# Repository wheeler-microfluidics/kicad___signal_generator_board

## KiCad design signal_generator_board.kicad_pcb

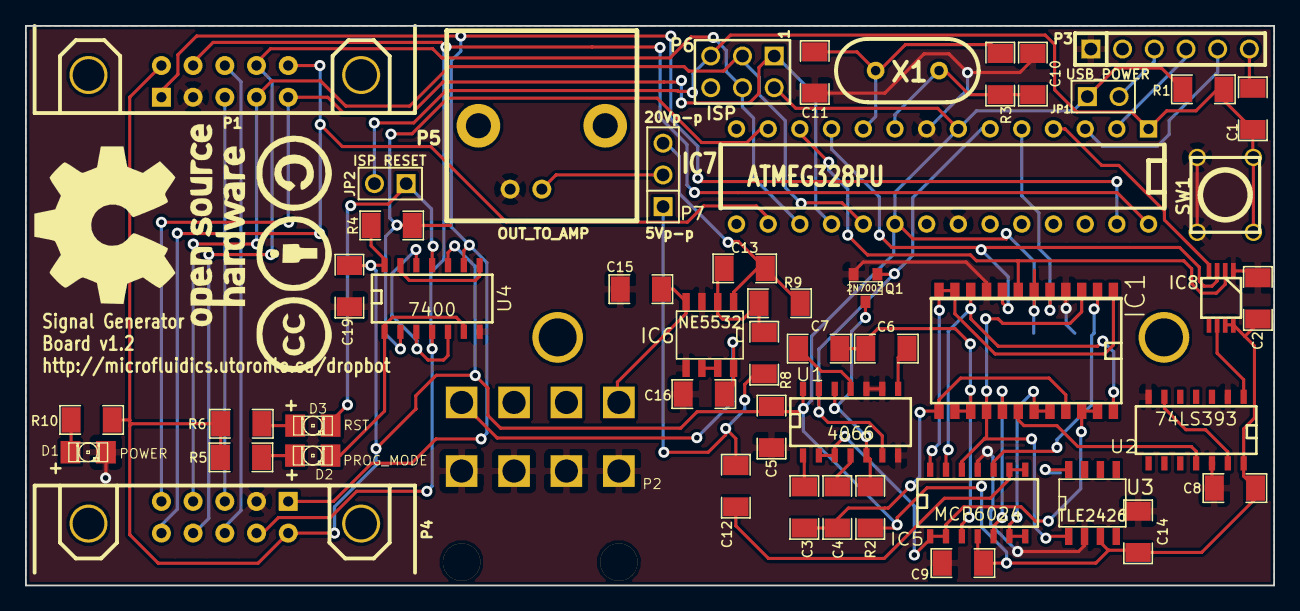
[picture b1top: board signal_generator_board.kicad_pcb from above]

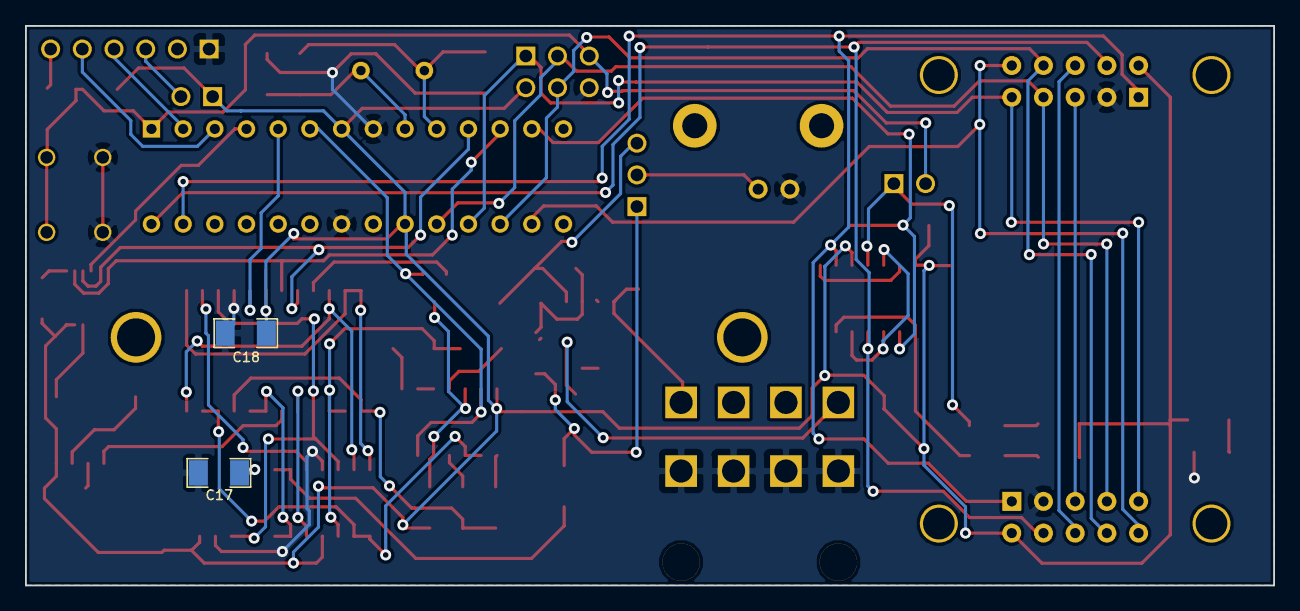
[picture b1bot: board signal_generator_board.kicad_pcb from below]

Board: 2 copper layers, 100.0 x 44.8 mm, 54 parts (2 on the bottom side), 56 nets.

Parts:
1PIN, 1PIN#2: P***; 1pin
C1, C2, C5, C8, C9, C14, C15, C16, C17, C18, C19: 0.1uF; SM1206
C3: 47nF; SM1206
C4: 4.7nF; SM1206
C6: 6.8nF; SM1206
C7: 680pF; SM1206
C10, C11: 22pF; SM1206
C12: 1uF; SM1206
C13: 5pF; SM1206
D1: POWER; LED-1206
D2: PROG_MODE; LED-1206
D3: RST; LED-1206
IC1: AD5206; SO24E
IC5: MCP6024; SO14E
IC6: NE5532; SO8E
IC7: ATMEG328PU; DIP-28
IC8: LTC6903/4; MSOP_8
JP1: USB_POWER; PIN_ARRAY_2X1
JP2: ISP RESET; PIN_ARRAY_2X1
P1, P4: CONN_10; HE10-10C
P2: CONN_8; Molex_4x2_Mini_Fit_Jr_RA
P3: CONN_6; PIN_ARRAY-6X1
P5: CONN_2; JACK_BNC
P6: CONN_6; pin_array_3x2
P7: CONN_3; PIN_ARRAY_3X1
Q1: 2N7002; SOT23
R1: 10k; SM1206
R2, R4, R5, R6, R10: 1k; SM1206
R3: 1Meg; SM1206
R8: 25k; SM1206
R9: 100k; SM1206
SW1: DPST; SW_PUSH_6mm
U1: 4066; SO14E
U2: 74LS393; SO14E
U3: TLE2426; SO8E
U4: 7400; SO14E
X1: 16MHz; HC-49V

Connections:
5Vp-p_WAVEOUT: C12.2, P7.1, R8.1
20Vp-p_WAVEOUT: C13.2, IC6.1, P7.3, R9.1
+5V_USB: JP1.2, P3.3
+12V: C16.2, IC6.8, P2.1
-12V: C15.1, IC6.4, P2.4
A4/SDA: IC7.27, P1.1, P4.1, U4.9
A5/SCL: IC7.28, P1.4, P4.4, U4.4
C1A: C3.1, C4.1, IC1.13, IC1.21
C1B: IC1.22, IC1.23, IC5.1, IC5.2, U1.2, U1.3
C2A: C6.1, C7.1, IC1.14, IC1.15, IC5.3
D2/LTC6904_SS: IC7.4, IC8.4
D3/AD5206_SS: IC1.5, IC7.5
D4/FREQ_RANGE: IC7.6, Q1.1, U1.6, U1.13
D5/S_SCK: IC1.8, IC7.11, IC8.3
D6/S_MOSI: IC1.7, IC7.12, IC8.2
D7/ISP_ENABLE: IC7.13, R4.2, U4.2
D10/SS: IC7.16, P1.10, P4.10
D11/MOSI: IC7.17, P1.8, P4.8, P6.4
D12/MISO: IC7.18, P1.9, P4.9, P6.1
D13/SCK: IC7.19, P1.7, P4.7, P6.3
GND: C2.2, C5.1, C8.1, C9.2, C10.1, C11.1, C14.2, C15.2, C16.1, C17.1, C18.2, C19.1, D1.2, IC1.4, IC1.9, IC5.11, IC6.3, IC6.5, IC7.8, IC7.22, IC8.1, P1.3, P2.5, P2.6, P2.7, P2.8, P3.1, P4.3, P5.1, P6.6, Q1.2, SW1.2, SW1.4, U1.7, U1.9, U1.10, U2.2, U2.7, U2.12, U3.2, U4.7
unnamed: IC8.6, U2.1
unnamed: IC6.6, IC6.7
unnamed: U2.6, U2.13
unnamed: IC1.18, U2.11
unnamed: IC1.17, IC5.5
unnamed: IC1.2, IC5.10
unnamed: C12.1, IC5.8, IC5.9
unnamed: IC1.10, IC1.24, IC5.13
unnamed: Q1.3, R2.2, U1.5, U1.12
unnamed: C3.2, U1.1
unnamed: C4.2, U1.4
unnamed: C6.2, U1.8
unnamed: C7.2, U1.11
unnamed: P1.6, P4.6
unnamed: C1.1, P3.6
unnamed: P1.5, P4.5
unnamed: U4.8, U4.13
unnamed: D3.1, R6.2
unnamed: D3.2, JP2.1, U4.11
unnamed: D2.1, R5.2
unnamed: D2.2, U4.1, U4.6
unnamed: IC1.1, IC1.11, IC1.12, IC5.14
unnamed: IC1.19, IC1.20, IC5.6, IC5.7
unnamed: C17.2, U3.8
unnamed: U4.3, U4.5, U4.12
unnamed: C13.1, IC6.2, R8.2, R9.2
unnamed: D1.1, R10.1
unnamed: C11.2, IC7.10, R3.2, X1.1
unnamed: C10.2, IC7.9, R3.1, X1.2
RST: C1.2, IC7.1, JP2.2, P6.5, R1.1, SW1.1, SW1.3
RX: IC7.3, P3.5
TX: IC7.2, P3.4
VCC: C2.1, C5.2, C8.2, C9.1, C14.1, C18.1, C19.2, IC1.6, IC5.4, IC7.7, IC7.20, IC8.7, IC8.8, JP1.1, P1.2, P4.2, P6.2, R1.2, R2.1, R4.1, R5.1, R6.1, R10.2, U1.14, U2.14, U3.3, U4.10, U4.14
VGND: IC1.3, IC1.16, IC5.12, U3.1
WAVEOUT: P5.2, P7.2

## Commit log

2013-08-26 v1.0
2013-08-29 Add missing parts to BOM
2013-09-03 Fix link on BOM
2013-09-11 Add paste and pos files
2013-09-19 Make drill file compatible with gerbmerge
2013-10-09 Swap ATmega328 for ATmega328P on BOM
    Makes it easier to flash Arduino bootloader
2013-10-09 Add note to BOM about optional cap (C13)
2013-10-09 Add shunts to BOM
2013-10-24 Change C4 and C7 (update BOM)
2013-12-18 Fix #37
    Remove DC bias from 5 Vpk-pk output
2014-05-08 Add ISP prgramming, replace 0603 caps with 1206, ...
    * add polarity labels to LEDs
2014-05-28 Fix BOM, labels, modify to use soft/bitbanged SPI
2014-07-24 Fix part number on BOM for P3
2014-08-05 Update pos files
2015-02-05 Add docs
2015-02-17 Fix part number for P3 on BOM
2015-02-24 Add BNC nut and lock washer to BOM
2015-03-12 Fix frequency divisor on schematic (32, not 16)
2016-01-20 Update .gitmodules file to point to github
2017-07-13 added appveyor.yml
2017-07-14 AppVeyor Configuration Updated
2017-07-15 AppVeyor Update: "5f61b891681557a9814440e47f9102b18ddcac59"
2017-07-17 AppVeyor Update: "ebd3acae5fa1c3216efbc6cb908b5db07f7b5100"
2017-07-17 AppVeyor Update: "f9cc8f1957b59965408d0c40c51fe03863cbf7a2"
2017-07-17 AppVeyor Update: "5d17439f61475bc23d95e0b42b680d8fb34545a9"
2017-07-18 AppVeyor Update: "ed2efe62bb2ab97aa8e77d59d2fbf27f7906765d"
2017-07-18 AppVeyor Update: "a4e909ac7a44d2708564d46a9b978b95c8367686"
2017-07-19 AppVeyor Update: "d5d159050eac48ab9123f383fe8e949476d7f60f"
2017-07-20 AppVeyor Update: "35852f667457a927c170bb71278740b12d7a8f75"
